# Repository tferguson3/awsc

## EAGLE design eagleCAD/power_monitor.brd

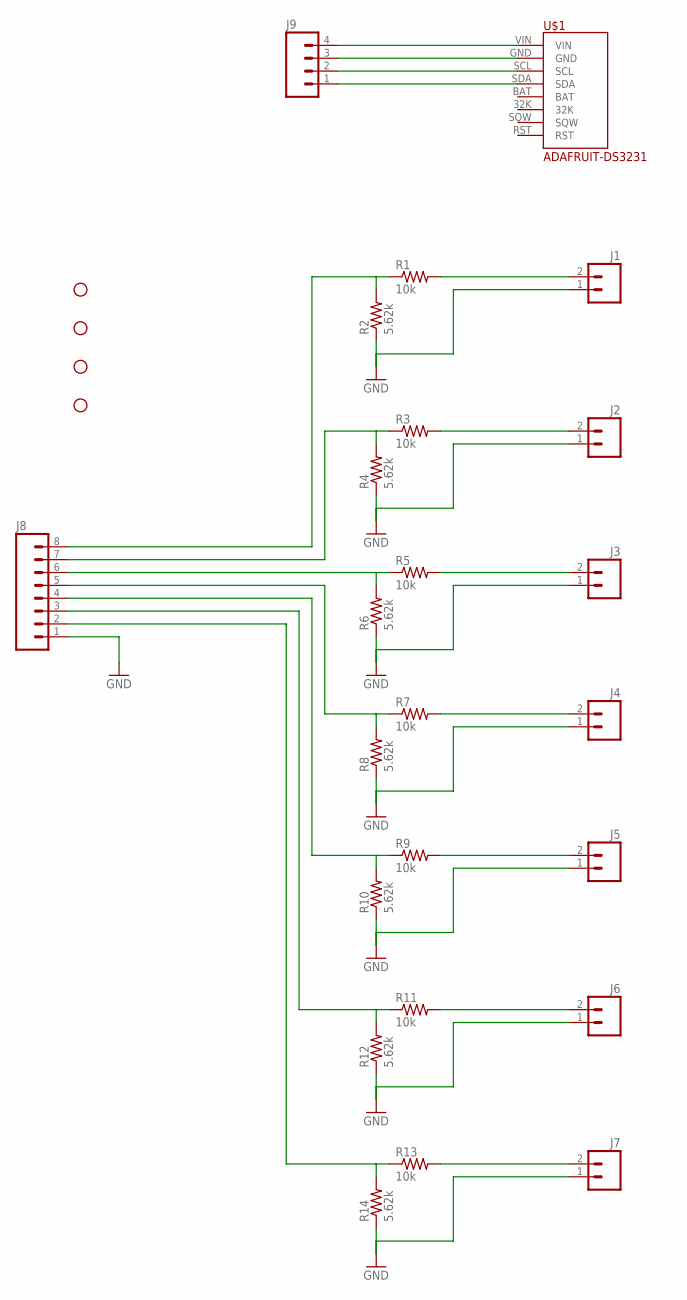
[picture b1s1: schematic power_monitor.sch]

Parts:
H1, H2, H3, H4: STAND-OFF
J1, J2, J3, J4, J5, J6, J7: M02LOCK_LONGPADS; 1X02_LOCK_LONGPADS
J8: M08LOCK_LONGPADS; 1X08_LOCK_LONGPADS
J9: M04LOCK_LONGPADS; 1X04_LOCK_LONGPADS
R1, R3, R5, R7, R9, R11, R13: 10k; AXIAL-0.3EZ
R2, R4, R6, R8, R10, R12, R14: 5.62k; AXIAL-0.3EZ
U$1: ADAFRUIT-DS3231

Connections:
GND: J1.1, J2.1, J3.1, J4.1, J5.1, J6.1, J7.1, J8.1, R2.P$1 (1), R4.P$1 (1), R6.P$1 (1), R8.P$1 (1), R10.P$1 (1), R12.P$1 (1), R14.P$1 (1)
unnamed: J2.2, R3.P$2 (2)
unnamed: J1.2, R1.P$2 (2)
unnamed: J8.8, R1.P$1 (1), R2.P$2 (2)
unnamed: J8.7, R3.P$1 (1), R4.P$2 (2)
unnamed: J3.2, R5.P$2 (2)
unnamed: J8.6, R5.P$1 (1), R6.P$2 (2)
unnamed: J4.2, R7.P$2 (2)
unnamed: J8.5, R7.P$1 (1), R8.P$2 (2)
unnamed: J5.2, R9.P$2 (2)
unnamed: J8.4, R9.P$1 (1), R10.P$2 (2)
unnamed: J6.2, R11.P$2 (2)
unnamed: J8.3, R11.P$1 (1), R12.P$2 (2)
unnamed: J7.2, R13.P$2 (2)
unnamed: J8.2, R13.P$1 (1), R14.P$2 (2)
unnamed: J9.4, U$1.VIN
unnamed: J9.3, U$1.GND
unnamed: J9.2, U$1.SCL
unnamed: J9.1, U$1.SDA

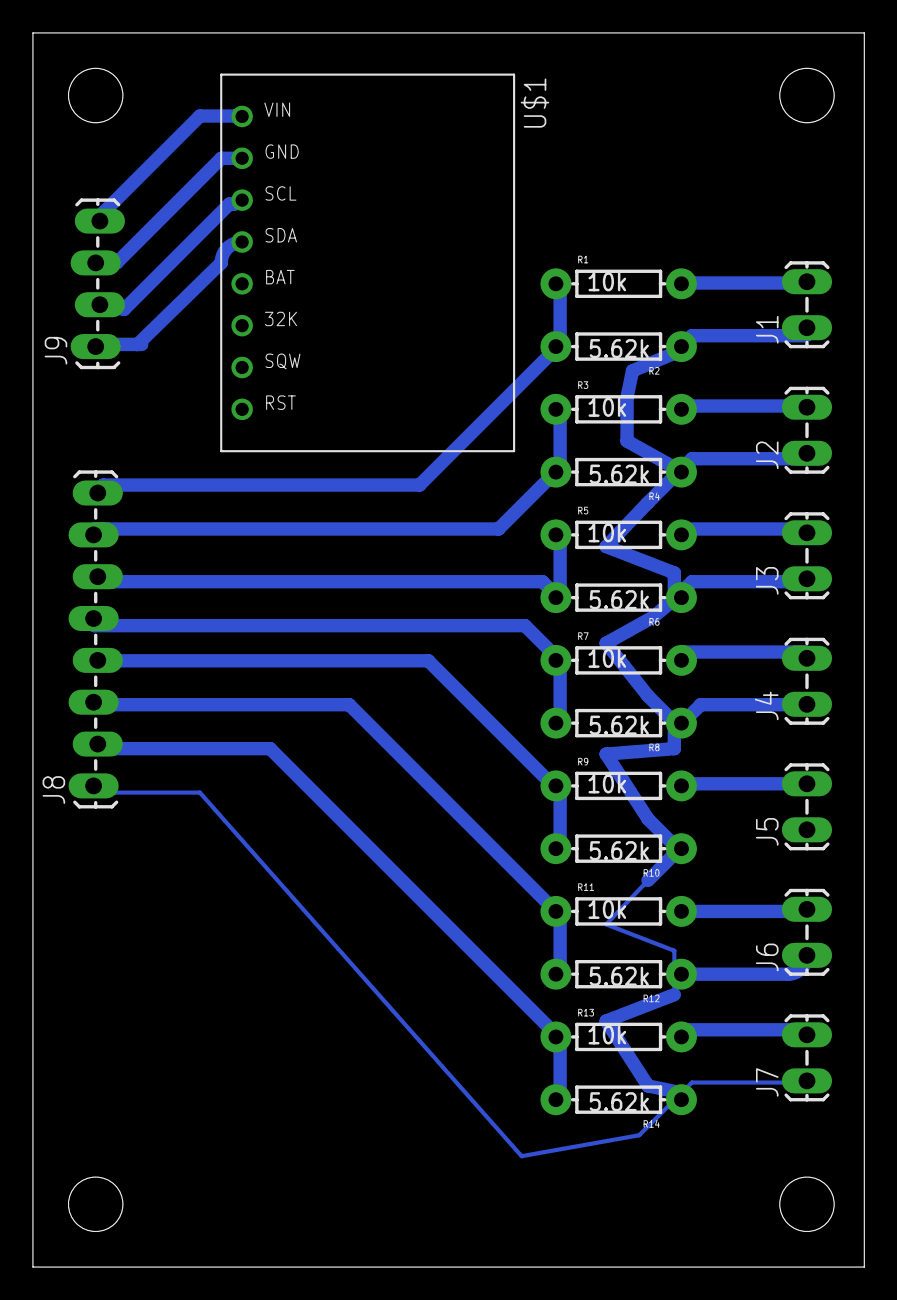
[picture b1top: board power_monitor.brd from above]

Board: 2 copper layers, 50.5 x 74.9 mm, 28 parts (0 on the bottom side), 19 nets.

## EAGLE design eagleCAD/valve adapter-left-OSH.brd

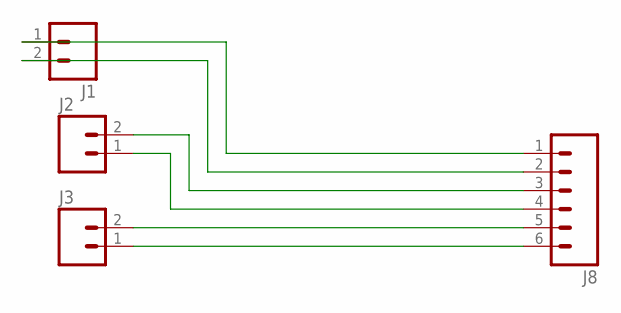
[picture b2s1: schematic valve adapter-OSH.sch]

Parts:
J1, J2, J3: M025MM; SCREWTERMINAL-5MM-2
J8: M06LOCK_LONGPADS; 1X06_LOCK_LONGPADS

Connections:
unnamed: J1.1, J8.1
unnamed: J1.2, J8.2
unnamed: J2.2, J8.3
unnamed: J2.1, J8.4
unnamed: J3.2, J8.5
unnamed: J3.1, J8.6

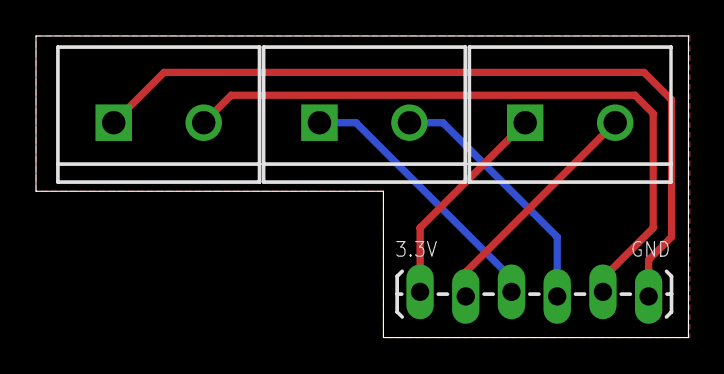
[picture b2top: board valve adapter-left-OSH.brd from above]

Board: 2 copper layers, 36.2 x 16.8 mm, 4 parts (0 on the bottom side), 6 nets.

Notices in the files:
parts and their libraries:
SparkFun-Connectors: Licensing: Creative Commons ShareAlike 4.0 International - https://creativecommons.org/licenses/by-sa/4.0
